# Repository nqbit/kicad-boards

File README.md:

# kicad-boards

### BeMicro Max 10 Development Board Template

Created a little board template for http://www.alterawiki.com/wiki/BeMicro_Max_10.

### SWD Shifter

The ST-Link/V2 debugger does not perform level shifting properly, the SWD Shifter translates the levels appropriately from the the ST-Link debugger.

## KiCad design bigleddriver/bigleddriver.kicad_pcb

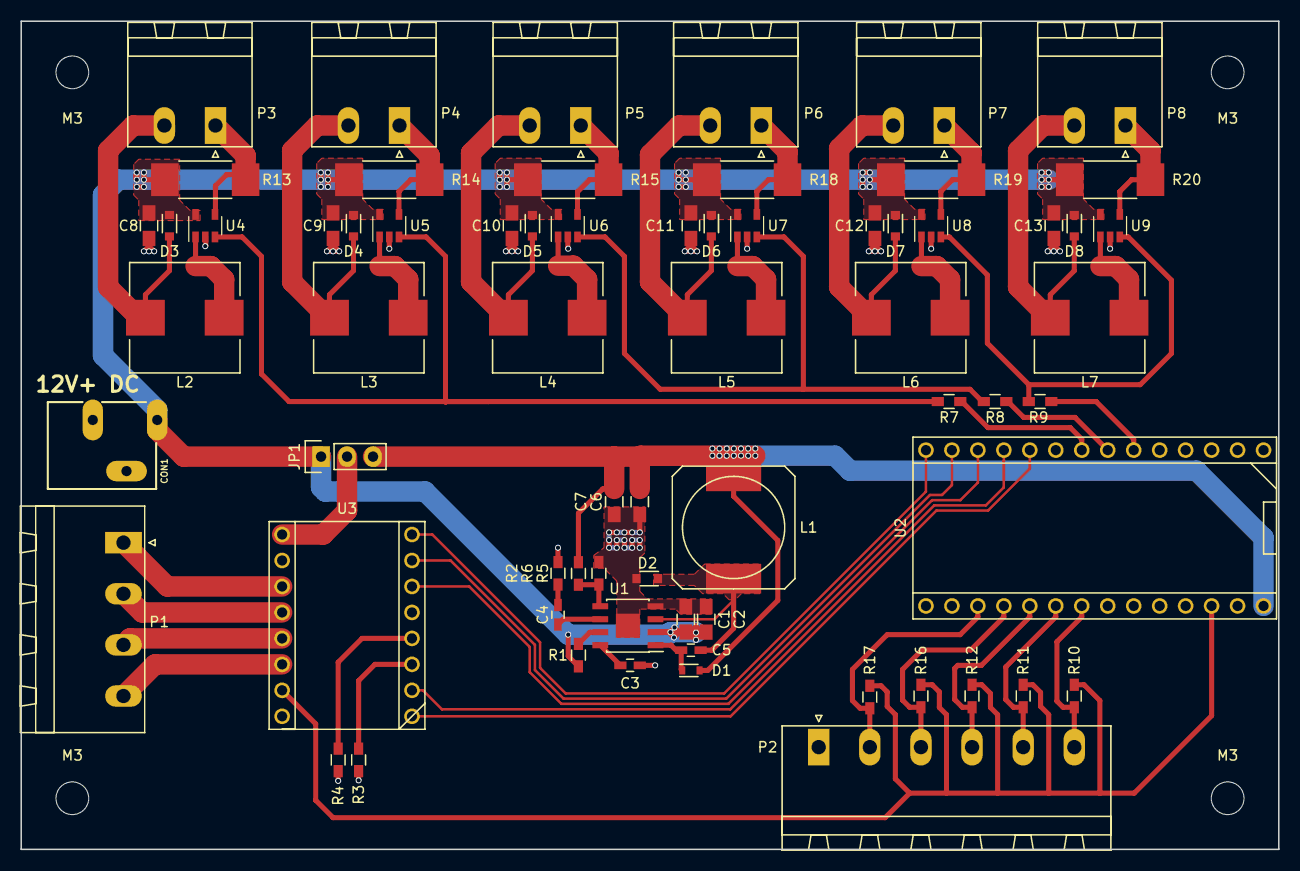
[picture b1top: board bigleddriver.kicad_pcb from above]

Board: 2 copper layers, 123.0 x 81.0 mm, 71 parts (0 on the bottom side), 52 nets.

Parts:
C1, C2, C8, C9, C10, C11, C12, C13: 10uF; C_0805_HandSoldering
C3: 0.1uF; C_0603_HandSoldering
C4: 3.9nF; C_0603_HandSoldering
C5: 10nF; C_0603_HandSoldering
C6, C7: 22uF; C_0805_HandSoldering
CON1: DC_BARREL_JACK; POWER_JACK_SLOT
D1: IN4148; D_0603
D2: MBRS130; D_0805
D3, D4, D5, D6, D7, D8: 1N5819; D_0805
JP1: Jumper_NC_Dual; Pin_Header_Straight_1x03
L1: 10uH; SELF-WE-PD-XXL
L2, L3, L4, L5, L6, L7: 100uH; Inductor_Wurth_HCI-1030
M3, M3#2, M3#3, M3#4: MountingHole_3.2mm_M3
P1: CONN_01X04; PhoenixContact_MSTBA-G_04x5.00mm_Angled
P2: CONN_01X06; PhoenixContact_MSTBA-G_06x5.00mm_Angled
P3, P4, P5, P6, P7, P8: CONN_01X02; PhoenixContact_MSTBA-G_02x5.00mm_Angled
R1: 100k; R_0603_HandSoldering
R2: 6.8k; R_0603_HandSoldering
R3, R4: 0; R_0603_HandSoldering
R5, R10, R11, R12, R16, R17: 10k; R_0603_HandSoldering
R6: 44.2k; R_0603_HandSoldering
R7, R8, R9: 22; R_0603_HandSoldering
R13, R14, R15, R18, R19, R20: 0.3; R_2512_HandSoldering
U1: MP2307; SOIC-8-1EP_3.9x4.9mm_Pitch1.27mm
U2: TEENSY_3.2
U3: STEP_STICK_TMC2208; TMC2208_SILENTSTEPSTICK
U4, U5, U6, U7, U8, U9: AL8861; SOT-23-5

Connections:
+5V: C6.1, C7.1, D1.2, JP1.3, L1.2, R6.2, U2.28
+12V: C1.1, C2.1, C8.1, C9.1, C10.1, C11.1, C12.1, C13.1, CON1.PWR, D3.1, D4.1, D5.1, D6.1, D7.1, D8.1, JP1.1, R1.2, R13.2, R14.2, R15.2, R18.2, R19.2, R20.2, U1.2, U4.5, U5.5, U6.5, U7.5, U8.5, U9.5
/BTN0: P2.6, R10.2, U2.21
/BTN1: P2.5, R11.2, U2.20
/BTN2: P2.4, R12.2, U2.19
/BTN3: P2.3, R16.2, U2.18
/BTN4: P2.2, R17.2, U2.17
/M1-A: P1.3, U3.13
/M1-B: P1.4, U3.14
/M2-A: P1.2, U3.12
/M2-B: P1.1, U3.11
/MOTOR_DIR: U2.10, U3.1
/MOTOR_EN: U2.14, U3.8
/MOTOR_MS1: U2.13, U3.7
/MOTOR_MS2: U2.12, U3.6
/MOTOR_STEP: U2.11, U3.2
/PWM_B: R9.1, U8.3, U9.3
/PWM_G: R8.1, U6.3, U7.3
/PWM_R: R7.1, U4.3, U5.3
/SW: C5.2, D2.1, L1.1, U1.3
/VIO: R10.1, R11.1, R12.1, R16.1, R17.1, U2.26, U3.15
GND: C1.2, C2.2, C3.2, C6.2, C7.2, C8.2, C9.2, C10.2, C11.2, C12.2, C13.2, CON1.GND@, D2.2, P2.1, R2.1, R3.2, R4.2, R5.2, U1.4, U1.9, U2.1, U2.27, U3.10, U3.16, U4.2, U5.2, U6.2, U7.2, U8.2, U9.2
unnamed: C3.1, U1.8
unnamed: C4.1, U1.6
unnamed: C4.2, R2.2
unnamed: C5.1, D1.1, U1.1
unnamed: D3.2, L2.2, P3.2
unnamed: D4.2, L3.2, P4.2
unnamed: D5.2, L4.2, P5.2
unnamed: D6.2, L5.2, P6.2
unnamed: D7.2, L6.2, P7.2
unnamed: D8.2, L7.2, P8.2
unnamed: L2.1, U4.1
unnamed: L3.1, U5.1
unnamed: L4.1, U6.1
unnamed: L5.1, U7.1
unnamed: L6.1, U8.1
unnamed: L7.1, U9.1
unnamed: P3.1, R13.1, U4.4
unnamed: P4.1, R14.1, U5.4
unnamed: P5.1, R15.1, U6.4
unnamed: P6.1, R18.1, U7.4
unnamed: P7.1, R19.1, U8.4
unnamed: P8.1, R20.1, U9.4
unnamed: R1.1, U1.7
unnamed: R3.1, U3.3
unnamed: R4.1, U3.4
unnamed: R5.1, R6.1, U1.5
unnamed: R7.2, U2.8
unnamed: R8.2, U2.7
unnamed: R9.2, U2.6
VMOTOR: JP1.2, U3.9

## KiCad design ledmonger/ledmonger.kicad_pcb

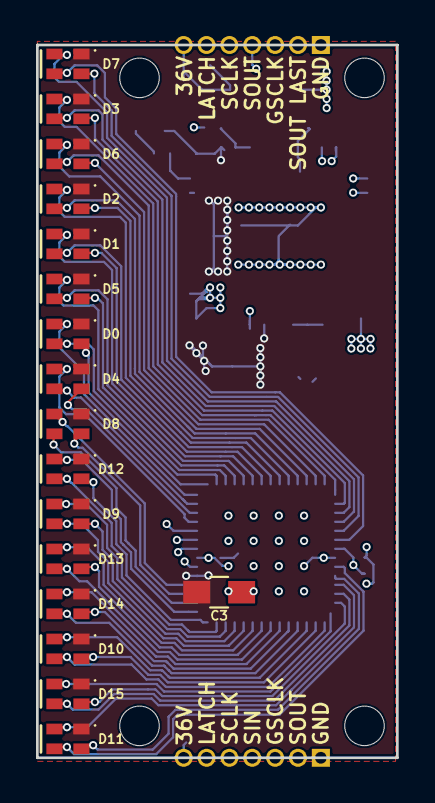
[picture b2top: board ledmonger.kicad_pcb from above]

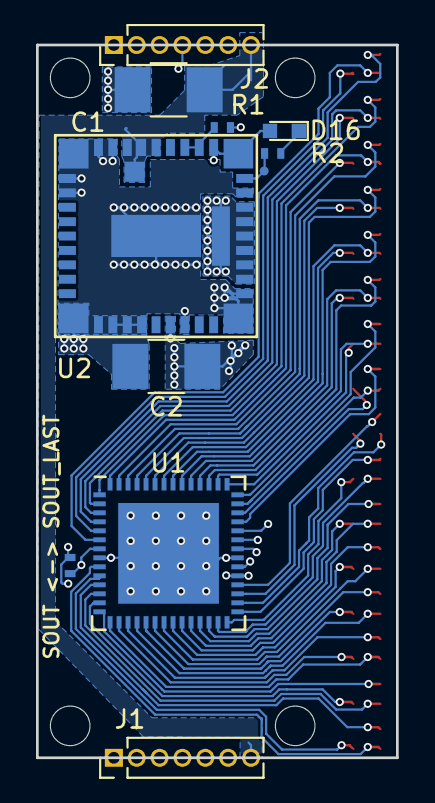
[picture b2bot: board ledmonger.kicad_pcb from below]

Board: 4 copper layers, 20.0 x 39.6 mm, 28 parts (11 on the bottom side), 60 nets.

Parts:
C1, C2: 100uF; C_1210_HandSoldering
C3: 100nF; C_0805_HandSoldering
D0, D1, D2, D3, D4, D5, D6, D7, D8, D9, D10, D11, D12, D13, D14, D15: LED_ARGB; LED_HSMF-C114
D16: LED_Small; LED_0603
J1, J2: Conn_01x07; Pin_Header_Straight_1x07_Pitch1.27mm
JP1: Jumper_NC_Small; R_0402_NoSilk
R1, R2: 8.06k; R_0402_NoSilk
TP0: PWRGD; TEST_POINT_0.5mm
U1: TLC5955; QFN-56-1EP_7x7mm_Pitch0.5mm
U2: LMZ34202; 43-BQFN-10mmx10mm

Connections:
+3V3: C2.1, C3.1, D0.1, D1.1, D2.1, D3.1, D4.1, D5.1, D6.1, D7.1, D8.1, D9.1, D10.1, D11.1, D12.1, D13.1, D14.1, D15.1, D16.2, U1.33, U2.7, U2.13, U2.14, U2.15, U2.16, U2.17, U2.18, U2.21, U2.22, U2.43
/GSCLK: J1.3, J2.3, U1.34
/LAT: J1.6, J2.6, U1.38
/LEDB0: D0.4, U1.42
/LEDB1: D1.4, U1.48
/LEDB2: D2.4, U1.51
/LEDB3: D3.4, U1.1
/LEDB4: D4.4, U1.39
/LEDB5: D5.4, U1.45
/LEDB6: D6.4, U1.54
/LEDB7: D7.4, U1.4
/LEDB8: D8.4, U1.32
/LEDB9: D9.4, U1.26
/LEDB10: D10.4, U1.17
/LEDB11: D11.4, U1.11
/LEDB12: D12.4, U1.29
/LEDB13: D13.4, U1.23
/LEDB14: D14.4, U1.20
/LEDB15: D15.4, U1.14
/LEDG0: D0.3, U1.44
/LEDG1: D1.3, U1.50
/LEDG2: D2.3, U1.53
/LEDG3: D3.3, U1.3
/LEDG4: D4.3, U1.41
/LEDG5: D5.3, U1.47
/LEDG6: D6.3, U1.56
/LEDG7: D7.3, U1.6
/LEDG8: D8.3, U1.30
/LEDG9: D9.3, U1.24
/LEDG10: D10.3, U1.15
/LEDG11: D11.3, U1.9
/LEDG12: D12.3, U1.27
/LEDG13: D13.3, U1.21
/LEDG14: D14.3, U1.18
/LEDG15: D15.3, U1.12
/LEDR0: D0.2, U1.43
/LEDR1: D1.2, U1.49
/LEDR2: D2.2, U1.52
/LEDR3: D3.2, U1.2
/LEDR4: D4.2, U1.40
/LEDR5: D5.2, U1.46
/LEDR6: D6.2, U1.55
/LEDR7: D7.2, U1.5
/LEDR8: D8.2, U1.31
/LEDR9: D9.2, U1.25
/LEDR10: D10.2, U1.16
/LEDR11: D11.2, U1.10
/LEDR12: D12.2, U1.28
/LEDR13: D13.2, U1.22
/LEDR14: D14.2, U1.19
/LEDR15: D15.2, U1.13
/PWRGD: R2.2, TP0.1, U2.20
/SCLK: J1.5, J2.5, U1.37
/SIN: J1.4, U1.36
/SOUT: J2.4, JP1.1, U1.7
/SOUT_LAST: J1.2, J2.2, JP1.2
/V36P0: C1.1, J1.7, J2.7, U2.26, U2.27, U2.28, U2.42
/VADJ: R1.2, U2.23, U2.24
GND: C1.2, C2.2, C3.2, J1.1, J2.1, R1.1, U1.8, U1.35, U1.57, U2.1, U2.2, U2.3, U2.4, U2.5, U2.8, U2.11, U2.12, U2.19, U2.29, U2.30, U2.31, U2.32, U2.33, U2.41
unnamed: D16.1, R2.1

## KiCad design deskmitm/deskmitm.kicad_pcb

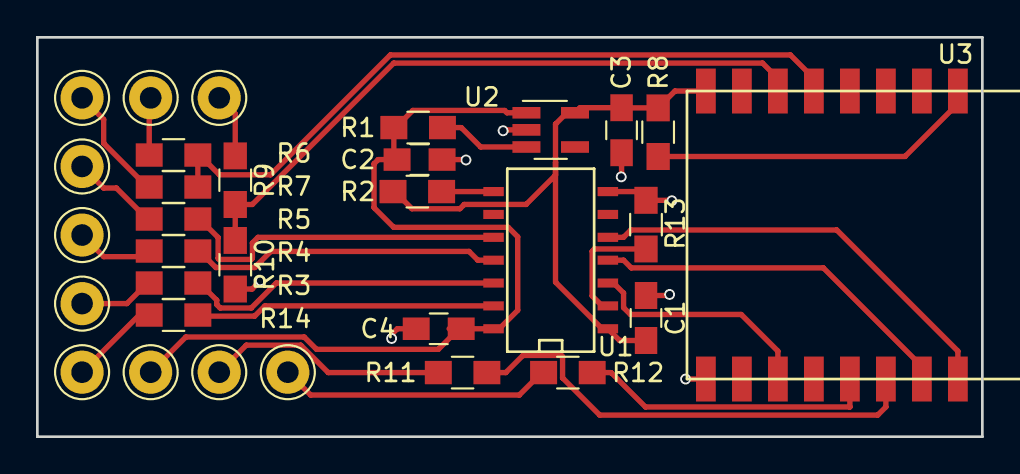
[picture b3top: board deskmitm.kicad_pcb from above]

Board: 2 copper layers, 52.5 x 22.2 mm, 31 parts (0 on the bottom side), 26 nets.

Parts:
C1, C4: 100nF; C_0805_HandSoldering
C2, C3: 10uF; C_0805_HandSoldering
J1, J2, J3, J4, J5, J6, J7, J8, J9, J10: Conn_01x01; Pin_d1.0mm_L10.0mm_LooseFit
R1, R2, R8, R11, R12, R13: 10k; R_0805_HandSoldering
R3, R4, R5, R6, R9, R14: 1k; R_0805_HandSoldering
R7, R10: 2k; R_0805_HandSoldering
U1: TXB0104; SOIC-14_N
U2: AP2112; SOT-23-5_HandSoldering
U3: ESP8266_12S; ESP8266_07

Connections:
+3V3: C1.1, C3.1, R2.2, R8.1, U1.1, U2.5, U3.8
+5V: C2.1, C4.1, J9.1, R1.2, U1.14, U2.1
/BTN_DOWN_IN: J1.1, R6.1
/BTN_DOWN_IN_LV: R6.2, R7.1, U3.5
/BTN_DOWN_OUT: J4.1, R12.1
/BTN_UP_IN: J2.1, R9.1
/BTN_UP_IN_LV: R9.2, R10.1, U3.6
/BTN_UP_OUT: J3.1, R11.1
/RX_FROM_POWER: J8.1, R5.1
/RX_FROM_POWER_LV: U1.5, U3.16
/RX_TO_DISPLAY: J5.1, R14.1
/RX_TO_DISPLAY_LV: R13.1, U1.2
/TX_FROM_POWER: J7.1, R4.1
/TX_FROM_POWER_LV: U1.4, U3.15
/TX_TO_DISPLAY: J6.1, R3.1
/TX_TO_DISPLAY_LV: U1.3, U3.11
GND: C1.2, C2.2, C3.2, C4.2, J10.1, R7.2, R10.2, R13.2, U1.7, U2.2, U3.9
unnamed: R1.1, U2.3
unnamed: R2.1, U1.8
unnamed: R3.2, U1.12
unnamed: R4.2, U1.11
unnamed: R5.2, U1.10
unnamed: R8.2, U3.1
unnamed: R11.2, U3.14
unnamed: R12.2, U3.13
unnamed: R14.2, U1.13

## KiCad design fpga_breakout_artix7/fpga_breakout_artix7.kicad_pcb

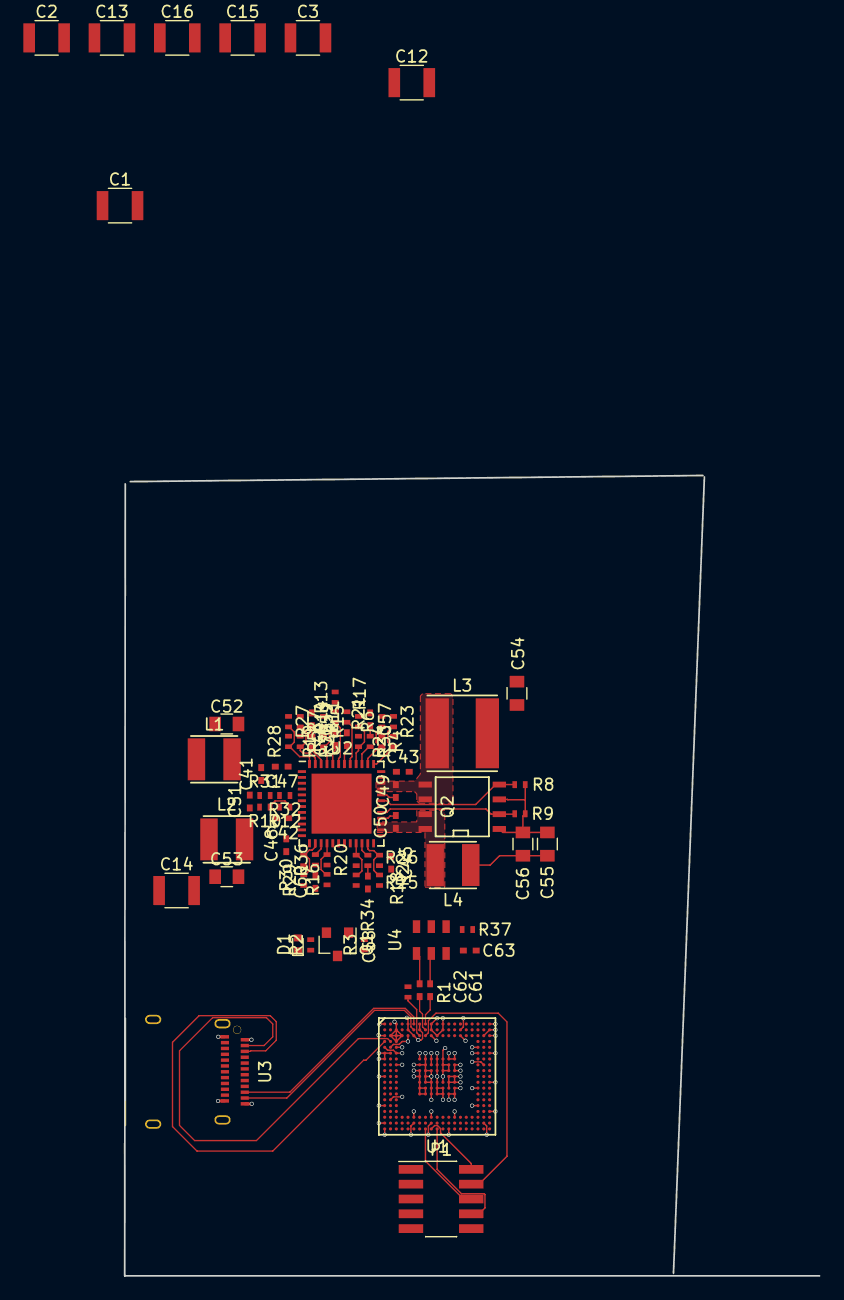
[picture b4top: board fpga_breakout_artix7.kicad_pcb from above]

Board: 4 copper layers, 59.6 x 68.6 mm, 112 parts (0 on the bottom side), 68 nets.

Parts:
C1, C13, C14, C15, C16: 100uF; C_1210
C2, C3, C12: 47uF; C_1210
C4, C6, C7, C8, C17, C18, C19, C20, C21, C22, C23, C24: 4.7uF; C_0805
C5, C9, C10, C11, C25, C26, C27, C28, C29, C30, C31, C32, C33, C34, C35, C36, C37, C38, C39, C40: 0.47uF; C_0603
C41, C42, C43, C44, C45, C46, C51: 1uF; C_0402_NoSilk
C47, C48, C49, C50, C61, C62, C63: 100nF; C_0402_NoSilk
C52, C53: 10uF; C_0805
C54: 100uF; C_0805
C55, C56: 22uF; C_0805
C57, C58, C59, C60: 2.7nF; C_0402_NoSilk
D1: LED; LED_0402
L1, L2: 4.7uH; SRN4018
L3: 2.2uH; SRN6045
L4: 3.3uH; SRN4018
P1: CONN_02X05; Pin_Header_Straight_2x05_Pitch1.27mm_SMD
Q1: MOSFET-N; SOT-23
Q2: FDS9926A; SOIC-8-N
R1: 100; R_0402_NoSilk
R2: 4.7k; R_0402_NoSilk
R3: 100k; R_0402_NoSilk
R4, R13: 0; R_0402_NoSilk
R5: 301k; R_0402_NoSilk
R6: 9.53k - DNP; R_0402_NoSilk
R7: 402k; R_0402_NoSilk
R8, R9: 47k; R_0402_NoSilk
R10: 1.91k; R_0402_NoSilk
R11, R17: 31.6k; R_0402_NoSilk
R12: 4.99k; R_0402_NoSilk
R14: 0 - DNP; R_0402_NoSilk
R15, R18: 10.5k; R_0402_NoSilk
R16, R21: 10.2k; R_0402_NoSilk
R19, R22: 41.2k; R_0402_NoSilk
R20: 20k; R_0402_NoSilk
R23, R24, R25, R26, R27, R28, R29, R30, R31, R32, R33, R34, R35, R36: 56.2k; R_0402_NoSilk
R37: 10k; R_0402_NoSilk
U1: XC7A15TCPG236; CPG236
U2: ADP5052; QFN-48-1EP_7x7mm_Pitch0.5mm
U3: USB-C; USB-C_SMT
U4: DSC1123

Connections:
/GTP0_RX_N: U1.A4, U3.B10
/GTP0_RX_P: U1.B4, U3.B11
/GTP0_TX_N: U1.D1, U3.A3
/GTP0_TX_P: U1.D2, U3.A2
/GTP1_RX_N: U1.A6, U3.A10
/GTP1_RX_P: U1.B6, U3.A11
/GTP1_TX_N: U1.A2, U3.B3
/GTP1_TX_P: U1.B2, U3.B2
/GTP_REF_CLK_N: C61.1, U1.A8
/GTP_REF_CLK_P: C62.1, U1.B8
/JTAG_TCK: P1.4, U1.C8
/JTAG_TDI: P1.8, U1.W10
/JTAG_TDO: P1.6, U1.W8
/JTAG_TMS: P1.2, U1.W9
/VCC3V3: C63.2, P1.1, R37.1, U4.6
/power/AVCC1V0: C52.1, L1.2, R15.1
/power/AVCC1V2: C53.1, L2.2, R16.1
/power/BST1: C49.1, U2.32
/power/BST2: C50.1, U2.28
/power/COMP1: R33.2, U2.39
/power/COMP2: R34.2, U2.22
/power/COMP3: R35.2, U2.46
/power/COMP4: R36.2, U2.15
/power/DL1: Q2.4, R8.2, U2.31
/power/DL2: Q2.2, R9.2, U2.29
/power/EN1: R23.2, R24.1, U2.37
/power/EN2: R25.2, R26.1, U2.23
/power/EN3: R27.2, R28.1, U2.48
/power/EN4: R29.2, R30.1, U2.14
/power/EN5: R31.2, R32.1, U2.5
/power/FB1: R17.2, R21.1, U2.40
/power/FB2: R18.2, R22.1, U2.21
/power/FB3: R15.2, R19.1, U2.45
/power/FB4: R16.2, R20.1, U2.16
/power/FB5: R10.1, R12.1, U2.6
/power/SS12: R4.2, R6.1, U2.38
/power/SS34: R5.2, R7.2, U2.47
/power/SW1: C49.2, L3.1, Q2.5, Q2.6, U2.33, U2.34
/power/SW2: C50.2, L4.1, Q2.7, Q2.8, U2.26, U2.27
/power/SW3: C47.2, L1.1, U2.3
/power/SW4: C48.2, L2.1, U2.10
/power/VCC1V0: C55.1, C56.1, L4.2, R18.1
/power/VCC1V8: C51.1, R12.2, U2.7
/power/VCC3V3: C54.1, D1.2, L3.2, R3.1, R17.1, R23.1, R25.1, R27.1, R29.1, R31.1, U2.8
/power/VCC5V0: C41.1, C42.1, C43.1, C45.1, U2.4, U2.9, U2.24, U2.25, U2.35, U2.36
/power/VREG: C44.1, R6.2, R7.1, R13.2, U2.44
AVCC1P0: U1.C1, U1.E1, U1.F3, U1.G9, U1.H9
AVCC1P2: R1.2, U1.B1, U1.C5, U1.E2, U1.G7
GND: C1.2, C2.2, C3.2, C4.2, C5.2, C6.2, C7.2, C8.2, C9.2, C10.2, C11.2, C12.2, C13.2, C14.2, C15.2, C16.2, C17.2, C18.2, C19.2, C20.2, C21.2, C22.2, C23.2, C24.2, C25.2, C26.2, C27.2, C28.2, C29.2, C30.2, C31.2, C32.2, C33.2, C34.2, C35.2, C36.2, C37.2, C38.2, C39.2, C40.2, C41.2, C42.2, C43.2, C44.2, C45.2, C46.2, C51.2, C52.2, C53.2, C54.2, C55.2, C56.2, C57.1, C58.1, C59.1, C60.1, C63.1, P1.3, P1.5, P1.9, Q1.3, Q2.1, Q2.3, R4.1, R5.1, R8.1, R9.1, R10.2, R11.2, R14.2, R19.2, R20.2, R21.2, R22.2, R24.2, R26.2, R28.2, R30.2, R32.2, U1.A1, U1.A3, U1.A5, U1.A7, U1.A9, U1.A11, U1.A19, U1.B3, U1.B5, U1.B7, U1.B9, U1.B11, U1.B14, U1.C2, U1.C3, U1.C4, U1.C6, U1.C10, U1.C19, U1.D3, U1.E3, U1.E17, U1.F1, U1.F2, U1.F19, U1.G1, U1.G8, U1.G11, U1.H7, U1.H8, U1.H11, U1.H12, U1.H18, U1.J8, U1.J9, U1.J11, U1.J12, U1.K8, U1.L8, U1.L9, U1.L11, U1.L19, U1.M9, U1.M13, U1.N9, U1.N12, U1.N13, U1.P2, U1.T19, U1.U6, U1.U9, U1.V18, U1.W1, U1.W12, U2.2, U2.11, U2.13, U2.17, U2.18, U2.19, U2.30, U2.49, U3.A1, U3.A12, U3.B1, U3.B12, U3.P, U4.3
unnamed: C46.1, U2.42
unnamed: C47.1, U2.1
unnamed: C48.1, U2.12
unnamed: C57.2, R33.1
unnamed: C58.2, R34.1
unnamed: C59.2, R35.1
unnamed: C60.2, R36.1
unnamed: C61.2, U4.5
unnamed: C62.2, U4.4
unnamed: D1.1, R2.1
unnamed: Q1.1, R3.2, U2.20
unnamed: Q1.2, R2.2
unnamed: R1.1, U1.C7
unnamed: R11.1, U2.41
unnamed: R13.1, R14.1, U2.43
unnamed: R37.2, U4.1
V1P0: C1.1, C2.1, C4.1, C5.1, C7.1, C9.1, C11.1, U1.G10, U1.H10, U1.J10, U1.L10, U1.M10, U1.M11, U1.N10, U1.N11
V1P8: C3.1, C6.1, C8.1, C10.1, U1.C9, U1.H13, U1.J13
V3P3: C12.1, C13.1, C14.1, C15.1, C16.1, C17.1, C18.1, C19.1, C20.1, C21.1, C22.1, C23.1, C24.1, C25.1, C26.1, C27.1, C28.1, C29.1, C30.1, C31.1, C32.1, C33.1, C34.1, C35.1, C36.1, C37.1, C38.1, C39.1, C40.1, U1.B19, U1.C14, U1.C18, U1.F17, U1.G12, U1.G13, U1.H3, U1.J7, U1.K1, U1.K7, U1.K12, U1.K13, U1.L7, U1.L12, U1.L13, U1.M7, U1.M8, U1.M12, U1.M17, U1.N7, U1.N8, U1.R1, U1.R17, U1.U13, U1.V1, U1.V6, U1.V9

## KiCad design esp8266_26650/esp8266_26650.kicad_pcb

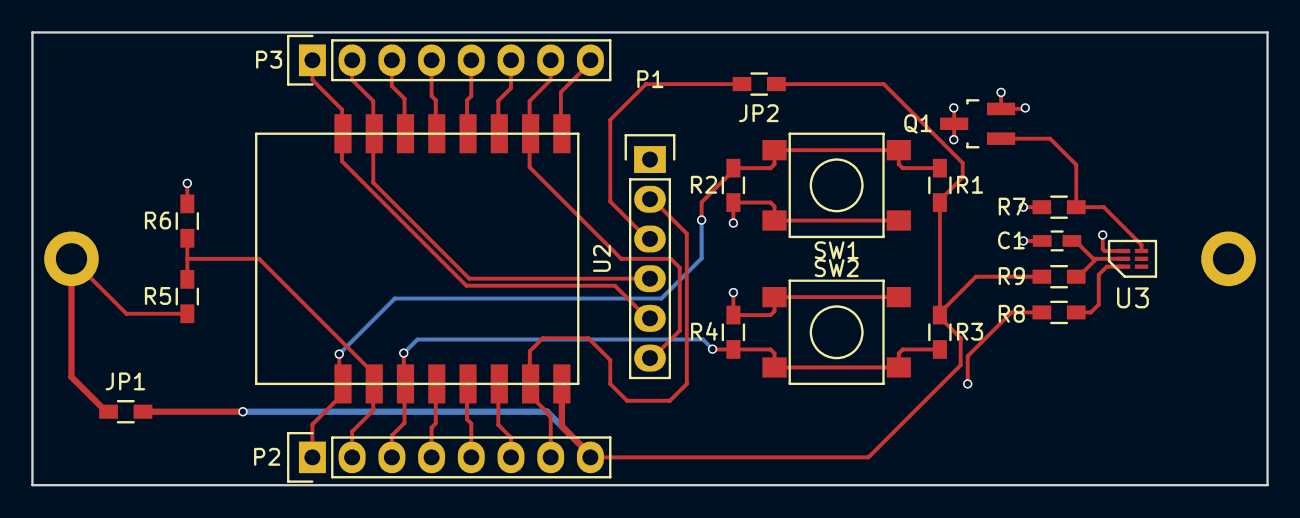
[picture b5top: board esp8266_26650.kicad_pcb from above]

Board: 2 copper layers, 79.0 x 29.0 mm, 21 parts (1 on the bottom side), 22 nets.

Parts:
C1: 0.1uF; C_0603_HandSoldering
JP1, JP2: JUMPER; R_0603_HandSoldering
P1: CONN_01X06; Pin_Header_Straight_1x06
P2, P3: CONN_01X08; Pin_Header_Straight_1x08
Q1: MMBF170; SOT-23_Handsoldering
R1, R2, R3, R4: 10k; R_0603_HandSoldering
R5: 260k; R_0603_HandSoldering
R6: 100k; R_0603_HandSoldering
R7: 5.1M; R_0603_HandSoldering
R8: 2.2k; R_0603_HandSoldering
R9: 330; R_0603_HandSoldering
SW1, SW2: SW_PUSH; B3S-1000P
U1: BATT_26650x1
U2: ESP8266_07
U3: BQ29705; WFDFN-6

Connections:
+BATT: JP1.1, R5.1, U1.1
/CH_PD: P2.3, R3.2, R4.1, SW2.2, U2.3
/DOUT: Q1.1, R7.1, U3.3
/FTDI_CTS: P1.2, P2.7, U2.7
/FTDI_RTS: P1.6, P3.7, U2.10
/FTDI_RX: P1.5, P3.1, U2.16
/FTDI_TX: P1.4, P3.2, U2.15
/FTDI_VCC: JP2.2, P1.3
/GPIO0: P3.5, U2.12
/GPIO1: P3.6, U2.11
/GPIO4: P3.4, U2.13
/GPIO5: P3.3, U2.14
/GPIO12: P2.6, U2.6
/GPIO14: P2.5, U2.5
/RESET: P2.1, R1.2, R2.1, SW1.2, U2.1
/VBAT_MON: P2.2, R5.2, R6.1, U2.2
/WAKE: P2.4, U2.4
GND: P1.1, P3.8, Q1.3, R2.2, R4.2, R6.2, R8.1, SW1.1, SW2.1, U2.9
unnamed: C1.1, R9.2, U3.5
unnamed: R8.2, U3.6
VCC: JP1.2, JP2.1, P2.8, R1.1, R3.1, R9.1, U2.8
VSS: C1.2, Q1.2, R7.2, U1.2, U3.4

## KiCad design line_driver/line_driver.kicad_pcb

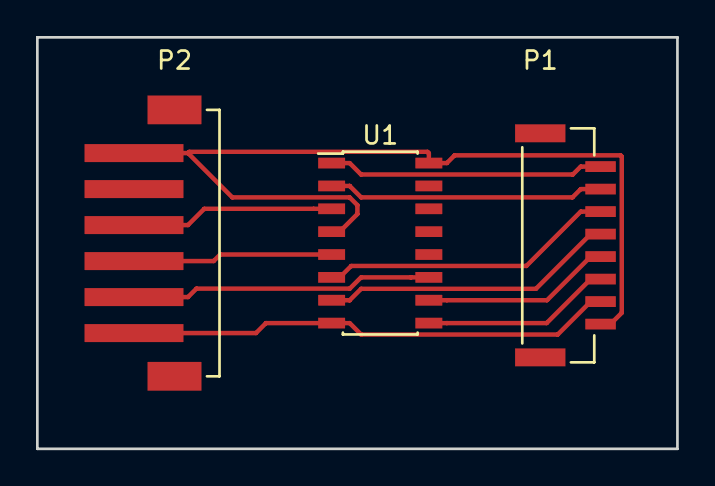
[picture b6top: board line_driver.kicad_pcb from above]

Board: 2 copper layers, 35.6 x 22.9 mm, 3 parts (0 on the bottom side), 11 nets.

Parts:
P1: CONN_01X08; GH_1x8_TOP
P2: CONN_01X06; CONN_PH_1x6_TOP_SMT
U1: AM26LS32ACDR; SOIC-16_3.9x9.9mm_Pitch1.27mm

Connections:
GND: P1.2, P2.6, U1.8
unnamed: P1.3, U1.9
unnamed: P1.4, U1.10
unnamed: P1.5, U1.7
unnamed: P1.6, U1.6
unnamed: P1.7, U1.2
unnamed: P1.8, U1.1
unnamed: P2.3, U1.3
unnamed: P2.4, U1.5
unnamed: P2.5, U1.11
VCC: P1.1, P2.1, U1.4, U1.16

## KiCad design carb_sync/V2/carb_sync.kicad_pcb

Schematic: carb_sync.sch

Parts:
12V1: 12V; Measurement_Point_Round-TH_Big
C1, C2, C3, C4, C5, C6: 100nF; C_0603_HandSoldering
C7, C8: C; c_elec_5x5.7
GND1: GND; Measurement_Point_Round-TH_Big
LCD1: ILI9341_Adafruit; ADAFRUIT_LCD
U1, U2, U3, U4, U5, U6: MPXV6115V
U7: TEENSY_3.2
U8: AP1117; TO-92_Horizontal1_Inline_Narrow_Oval

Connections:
+3V3: LCD1.3, U7.26
+5V: C8.1, LCD1.2, LCD1.39, U1.2 (VCC), U2.2 (VCC), U3.2 (VCC), U4.2 (VCC), U5.2 (VCC), U6.2 (VCC), U7.28, U8.2
+12V: 12V1.1, C7.1, U8.3
GND: C1.2, C2.2, C3.2, C4.2, C5.2, C6.2, C7.2, C8.2, GND1.1, LCD1.1, LCD1.40, U1.3 (GND), U2.3 (GND), U3.3 (GND), U4.3 (GND), U5.3 (GND), U6.3 (GND), U7.1, U7.27, U8.1
LCD_CLK: LCD1.4, U7.15
LCD_CS: LCD1.7, U7.12
LCD_D/C: LCD1.8, U7.11
LCD_MISO: LCD1.5, U7.14
LCD_MOSI: LCD1.6, U7.13
LCD_RST: LCD1.9, U7.10
TOUCH_X+: LCD1.12, U7.17
TOUCH_X-: LCD1.14, U7.19
TOUCH_Y+: LCD1.11, U7.16
TOUCH_Y-: LCD1.13, U7.18
VAC1: C1.1, U1.4 (VOUT), U7.21
VAC2: C2.1, U2.4 (VOUT), U7.23
VAC3: C3.1, U3.4 (VOUT), U7.25
VAC4: C4.1, U4.4 (VOUT), U7.20
VAC5: C5.1, U5.4 (VOUT), U7.22
VAC6: C6.1, U6.4 (VOUT), U7.24

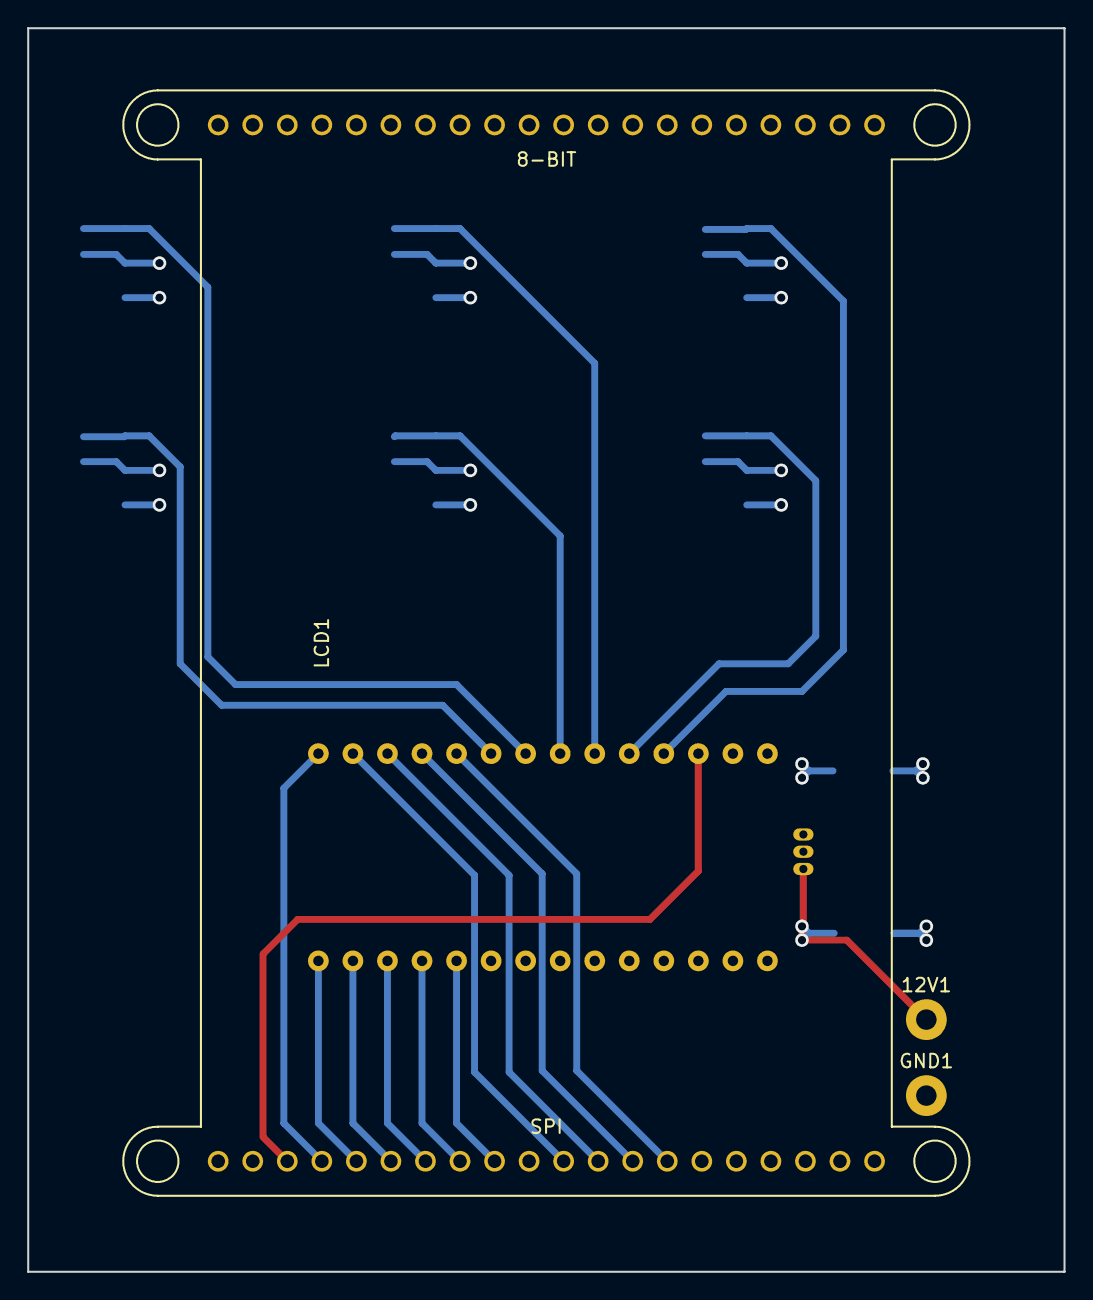
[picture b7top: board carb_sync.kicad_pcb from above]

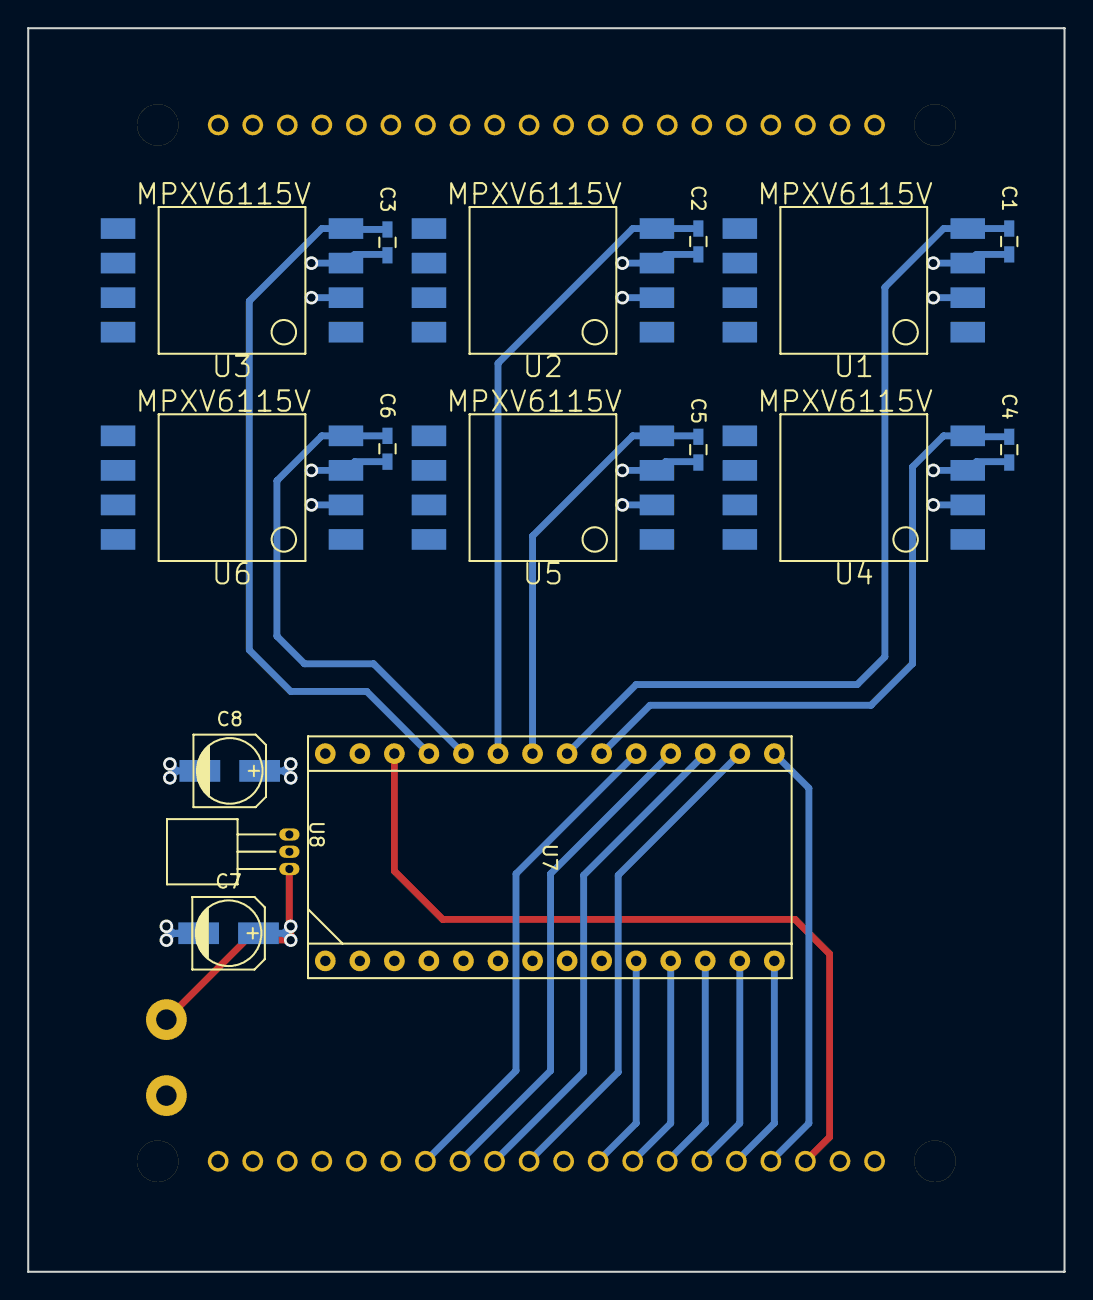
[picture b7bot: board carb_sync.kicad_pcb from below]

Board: 4 copper layers, 76.2 x 91.4 mm, 19 parts (16 on the bottom side), 20 nets.

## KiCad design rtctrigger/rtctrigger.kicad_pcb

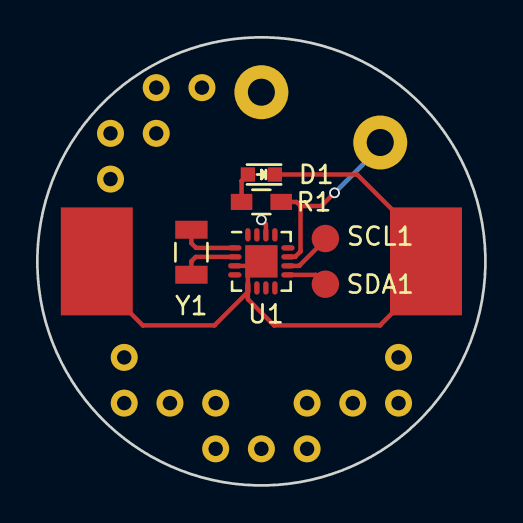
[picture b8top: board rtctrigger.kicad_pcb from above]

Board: 2 copper layers, 24.9 x 24.9 mm, 11 parts (1 on the bottom side), 8 nets.

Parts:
BATT1: BATT; PAD_7MM
BATT2: BATT; Measurement_Point_Round-TH_Big
D1: LED; LED_0603
GND1, GND2: GND; RECT_6X4MM
OUT1: OUT; Measurement_Point_Round-TH_Big
R1: 300; R_0603_HandSoldering
SCL1: SCL; Measurement_Point_Round-SMD-Pad_Small
SDA1: SDA; Measurement_Point_Round-SMD-Pad_Small
U1: M41T62; QFN-16-1EP_3x3mm_Pitch0.5mm
Y1: Crystal_Small; FC-135

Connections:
+BATT: BATT1.1, BATT2.1, U1.14
GND: D1.1, GND1.1, GND2.1, U1.3, U1.5, U1.17
unnamed: D1.2, R1.2
unnamed: OUT1.1, R1.1, U1.11
unnamed: SCL1.1, U1.10
unnamed: SDA1.1, U1.9
unnamed: U1.1, Y1.2
unnamed: U1.2, Y1.1

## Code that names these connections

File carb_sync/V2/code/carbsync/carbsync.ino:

#include <EEPROM.h>
#include <ILI9341_t3.h>
#include <SPI.h>
#include <TouchScreen.h>

#define MEM_MAGIC_ADDRESS 0
#define MEM_MAGIC_VALUE 0xDEADBEEF
#define SMOOTH_FACTOR_DEFAULT 0.99
#define SMOOTH_FACTOR_ADDRESS 4
#define SCALE_FACTOR_DEFAULT 0.3
#define SCALE_FACTOR_ADDRESS 8

#define DISP_X_OFFSET 0
#define DISP_Y_OFFSET 5
#define DISP_BAR_WIDTH 20
#define DISP_BAR_SPACING 20

#define FAST_DISP_X_OFFSET 20
#define FAST_DISP_Y_OFFSET 5
#define FAST_DISP_BAR_WIDTH 10
#define FAST_DISP_BAR_SPACING 30

#define VAC1 A5
#define VAC2 A7
#define VAC3 A9
#define VAC4 A4
#define VAC5 A6
#define VAC6 A8

// These are the four touchscreen analog pins
#define YP A0  // must be an analog pin, use "An" notation!
#define XM A3  // must be an analog pin, use "An" notation!
#define YM 16   // can be a digital pin
#define XP 15   // can be a digital pin

// This is calibration data for the raw touch data to the screen coordinates
#define TS_MINX 150
#define TS_MINY 120
#define TS_MAXX 920
#define TS_MAXY 940

#define MINPRESSURE 10
#define MAXPRESSURE 1000

#define TFT_DC  9
#define TFT_CS 10
#define TFT_SCLK 13
#define TFT_MOSI 11
#define TFT_MISO 12
#define TFT_RST 8

float SMOOTH_FACTOR = 0.99;
float LAST_SMOOTH_FACTOR = 0.99;
float SCALE_FACTOR = 0.3;
float LAST_SCALE_FACTOR = 0.3;

ILI9341_t3 tft = ILI9341_t3(TFT_CS, TFT_DC, TFT_RST, TFT_MOSI, TFT_SCLK, TFT_MISO);
TouchScreen ts = TouchScreen(XP, YP, XM, YM, 300);

float vac[6];
float vac_smooth[6] = {1023, 1023, 1023, 1023, 1023, 1023};
float vac_last[6];
float vac_smooth_last[6];
int vac_lu[] = {VAC1, VAC2, VAC3, VAC4, VAC5, VAC6};

enum Mode { Entry, Display, Config };

Mode mode = Display;
Mode last_mode = Entry;

class Button {
  public:
    Button(int x, int y, int w, int h) {
      _x = x;
      _y = y;
      _w = w;
      _h = h;
    }

    void draw() {
      uint16_t color = touched ? ILI9341_GREEN : ILI9341_YELLOW;
      tft.fillRoundRect(_x, _y, _w, _h, 10, color);
    }

    bool registerTouch(TSPoint p) {
      if (p.x < _x + _w && p.x > _x &&
          p.y < _y + _h && p.y > _y) {
        touched = true;
      } else {
        touched = false;
      }
      return touched;
    }

    bool isTouched() {
      return touched;
    }

  private:
    int _x;
    int _y;
    int _w;
    int _h;
    bool touched;
};

Button* buttons[4];

uint32_t getuint32(uint16_t addr)
{
  uint32_t val = 0;
  uint8_t val1 =  EEPROM.read(addr + 0) & 0xFF;
  uint8_t val2 =  EEPROM.read(addr + 1) & 0xFF;
  uint8_t val3 =  EEPROM.read(addr + 2) & 0xFF;
  uint8_t val4 =  EEPROM.read(addr + 3) & 0xFF;

  val = val1 | (val2 << 8) | (val3 << 16) | (val4 << 24);
  Serial.printf("getuint32: 0x%02x 0x%x 0x%x 0x%x 0x%02x\r\n", val1, val2, val3, val4, val);
  return val;
}

void setuint32(uint16_t addr, uint32_t val)
{
  uint8_t val1 = (val >> 0) & 0xFF;
  uint8_t val2 = (val >> 8) & 0xFF;
  uint8_t val3 = (val >> 16) & 0xFF;
  uint8_t val4 = (val >> 24) & 0xFF;

  EEPROM.write(addr + 0, val1);
  EEPROM.write(addr + 1, val2);
  EEPROM.write(addr + 2, val3);
  EEPROM.write(addr + 3, val4);

  Serial.printf("setuint32: 0x%02x 0x%02x 0x%02x 0x%02x 0x%02x\r\n", val1, val2, val3, val4, val);
}

void writeValues()
{
  setuint32(SMOOTH_FACTOR_ADDRESS, *((uint32_t*) &SMOOTH_FACTOR));
  setuint32(SCALE_FACTOR_ADDRESS, *((uint32_t*) &SCALE_FACTOR));
}

void writeMagic()
{
  setuint32(MEM_MAGIC_ADDRESS, (uint32_t) MEM_MAGIC_VALUE);
}


void readValues()
{
  uint32_t val1 = getuint32(SMOOTH_FACTOR_ADDRESS);
  uint32_t val2 = getuint32(SCALE_FACTOR_ADDRESS);
  SMOOTH_FACTOR = max(0.0, min(1.0, (float) * ((float*) &val1)));
  SCALE_FACTOR = max(0.0, min(1.0, (float) * ((float*) &val2)));
  LAST_SMOOTH_FACTOR = SMOOTH_FACTOR;
  LAST_SCALE_FACTOR = SCALE_FACTOR;
}

void restoreValues()
{
  uint32_t magic = getuint32(MEM_MAGIC_ADDRESS);

  if (magic != MEM_MAGIC_VALUE) {
    SMOOTH_FACTOR = SMOOTH_FACTOR_DEFAULT;
    SCALE_FACTOR = SCALE_FACTOR_DEFAULT;
    writeValues();
    writeMagic();
    Serial.println("Found NO magic");
  } else {
    readValues();
    Serial.println("Found magic");
  }
}
void setup(void) {


  tft.begin();
  tft.fillScreen(ILI9341_BLACK);

  tft.setTextColor(ILI9341_YELLOW);
  tft.setTextSize(2);
  tft.println("CarbSync");
  delay(200);
  tft.setRotation(2);
  tft.fillScreen(ILI9341_BLACK);

  Serial.begin(9600);
  Serial.println(tft.height());
  Serial.println(tft.width());

  buttons[0] = new Button(10, 50, 90, 70);
  buttons[1] = new Button(110, 50, 90, 70);
  buttons[2] = new Button(10, 150, 90, 70);
  buttons[3] = new Button(110, 150, 90, 70);

  restoreValues();
}


void loop()
{
  bool handled = false;

  // Retrieve a point
  TSPoint p = ts.getPoint();
  p.x = map(p.x, TS_MINX, TS_MAXX, 0, tft.width());
  p.y = map(p.y, TS_MINY, TS_MAXY, 0, tft.height());

  if (mode == Display) {
    for (int i = 0; i < 6; i++) {
      vac_last[i] = vac[i];
      vac[i] = 1023 - analogRead(vac_lu[i]) + 1;
      vac_smooth_last[i] = vac_smooth[i];
      vac_smooth[i] = vac[i] * (1 - SMOOTH_FACTOR) + vac_smooth[i] * SMOOTH_FACTOR;
    }

    for (int i = 0; i < 6; i++) {
      tft.fillRect(DISP_X_OFFSET + i * (DISP_BAR_WIDTH + DISP_BAR_SPACING), DISP_Y_OFFSET, DISP_BAR_WIDTH, vac_smooth[i]*SCALE_FACTOR, ILI9341_WHITE);
      tft.fillRect(DISP_X_OFFSET + i * (DISP_BAR_WIDTH + DISP_BAR_SPACING), vac_smooth[i]*SCALE_FACTOR + DISP_Y_OFFSET, DISP_BAR_WIDTH, 100, ILI9341_BLACK);

      tft.fillRect(FAST_DISP_X_OFFSET + i * (FAST_DISP_BAR_WIDTH + FAST_DISP_BAR_SPACING), FAST_DISP_Y_OFFSET, FAST_DISP_BAR_WIDTH, vac[i]*SCALE_FACTOR, ILI9341_RED);
      tft.fillRect(FAST_DISP_X_OFFSET + i * (FAST_DISP_BAR_WIDTH + FAST_DISP_BAR_SPACING), vac[i]*SCALE_FACTOR + FAST_DISP_Y_OFFSET, FAST_DISP_BAR_WIDTH, 500, ILI9341_BLACK);
    }
  } else {
    if (mode != last_mode) {
      tft.fillScreen(ILI9341_BLACK);
      tft.println("  CarbSync Config");
      tft.setCursor(10, 30);
      tft.setTextColor(ILI9341_WHITE);
      tft.print("Smooth + : -");
      tft.setCursor(10, 130);
      tft.print("Scale + : -");
      delay(100);
    } else {

      for (int i = 0; i < 4; i++) {
        handled = handled || buttons[i]->registerTouch(p);
        buttons[i]->draw();
      }

      if (buttons[0]->isTouched()) {
        SMOOTH_FACTOR = min(1.0, SMOOTH_FACTOR + 0.001);
        tft.fillRect(10, 250, tft.width(), 20, ILI9341_BLACK);
      }
      if (buttons[1]->isTouched()) {
        SMOOTH_FACTOR = max(0.0, SMOOTH_FACTOR - 0.001);
        tft.fillRect(10, 250, tft.width(), 20, ILI9341_BLACK);
      }
      tft.setCursor(10, 250);
      tft.print("Smooth: ");
      tft.print(SMOOTH_FACTOR);

      if (buttons[2]->isTouched()) {
        SCALE_FACTOR = min(1.0, SCALE_FACTOR + 0.001);
        tft.fillRect(10, 270, tft.width(), 20, ILI9341_BLACK);
      }
      if (buttons[3]->isTouched()) {
        SCALE_FACTOR = max(0.0, SCALE_FACTOR - 0.001);
        tft.fillRect(10, 270, tft.width(), 20, ILI9341_BLACK);
      }
      tft.setCursor(10, 270);
      tft.print("Scale: ");
      tft.print(SCALE_FACTOR);

    }
  }

  last_mode = mode;

  // we have some minimum pressure we consider 'valid'
  // pressure of 0 means no pressing!
  if (p.z < MINPRESSURE || p.z > MAXPRESSURE || handled) {
    return;
  }

  Serial.println(mode);

  // Handle Touch
  switch (mode) {
    case Display:
      mode = Config;
      tft.setRotation(0);
      tft.fillScreen(ILI9341_BLACK);
      break;
    case Config:
      mode = Display;
      if (LAST_SMOOTH_FACTOR != SMOOTH_FACTOR ||
          LAST_SCALE_FACTOR != SCALE_FACTOR) {
        writeValues();
      }
      LAST_SCALE_FACTOR = SCALE_FACTOR;
      LAST_SMOOTH_FACTOR = SMOOTH_FACTOR;
      tft.setRotation(2);
      tft.fillScreen(ILI9341_BLACK);
      break;
  }

  delay(500);
}

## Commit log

2015-01-31 [max10_template] Initial commit of the Altera BeMicro Max 10 development board.
2015-01-31 [readme] Initial commit.
2015-02-08 [carb_sync] Initial commit... WIP
2015-02-09 [carb_sync] Initial complete layout. LCD connector to pads.
2015-02-10 [carb_sync] Changed crystal footprint for ATMEGA328P.
2015-05-02 [arduino_template] Initial commit of the arduino template.
2015-05-02 [carb_sync] Upload of the released board files sent to fab.
2015-05-02 [scripts] Added a little helper script that renames the kicad generated gerbers.
2015-05-02 [boost_regulator_simple] Initial commit of a simple boost regulator.
    Currently incomplete, calculations and README to come.
2015-05-02 [boost_regulator_simple] First pass layout complete.
2015-05-02 [tools] Added a .gitignore file.
2015-05-02 [boost_regulator_simple] Updated schematic descriptions.
2015-05-02 [boost_regulator_simple] Added schematic pdf.
2015-05-02 [boost_regulator_simple] Cleaned up backup files from project.
2015-05-02 [boost_regulator_simple] Made changes to reduce EMI and other cosmetics.
2015-05-02 [tools] Updated gitignore to ignore more.
2015-05-02 [boost_regulator_simple] Extended Q1 copper pour ground plane and fixed silkscreen.
2015-05-02 [boost_regulator_simple] Added more filter caps to U1 and the inductor.
2015-05-02 [boost_regulator_simple] Off to fab!
2015-05-02 [boost_regulator_simple] Added full part datasheets and regenerated gerbers and schematic.
2015-05-03 [goproduino] Initial commit of the gopro connector breakout.
2015-10-06 [swd_shifter] Initial commit of the SWD shifter.
2015-10-06 [rfid-reader] Initial commit of the FSK demodulator circuit
2015-12-27 [dash_connector] Initial commit of the Amazon Dash debug connector breakout board.
2016-01-25 [swd_shifter] Add SWO line conversion from target to host.
2016-01-25 [swd_shifter] Added PDF schematic.
2016-02-09 [dash_connector] Fabbed board with MacroFab.
2016-02-09 [electricman] Fabbed with oshpark.
2016-02-09 [carb_sync] Move carb_sync v1 into separate folder.
2016-02-09 [carb_sync] Initial commit of V2. Still a work in progress.
2016-03-02 [rtctrigger] Initial commit of the rtc trigger board.
2016-03-02 [carb_sync] Add power supply filter caps and external voltage.
2016-03-05 [dash_connector] Fix pinout and add silkscreen.
2016-03-06 [dash_connector] Add new gerbers to connector.
2016-03-09 [line_driver] Initial commit of the diff/single line driver.
2016-03-12 [mini3d] initial commit of mini3d
2016-03-23 [mini3d] added current sensing
2016-03-23 [carbsync] V2: added code
2016-03-30 [carbsync] There are too many hacks to count
2016-03-31 [carbsync] Add persistent storage to variables.
2016-11-13 [esp8266_26650] initial commit
2016-11-27 [esp8266_26650] double checked footprint for esp and placed order.
2018-01-12 [fpga_breakout_artix7] Initial commit of the artix7 fpga gtp breakout board.
2018-01-30 [fpga_breakout_artix7] Added power supply and ufl connectors to schematic.
2018-02-02 [fpga_breakout_artix7] Progress on power supply schematic and layout.
2018-02-20 [fpga_breakout_artix7] Added USB-C connector, oscillator, and cleaned up power routing.
2018-05-28 [deskmitm] Initial commit of the desk mitm project.
2018-06-20 [ledmonger] Initial commit of the ledmonger.
    A basic breakout board for the TLC5955 led driver.
2018-06-26 [ledmonger] Improved layout and added castellated connector.
2018-06-27 [ledmonger] V1 ledmonger boards ordered.
2018-07-20 [qfn56pitchadapter] initial commit of 0.4 mm pitch to 0.5 mm pitch 56 pin + pad qfn adapter.
2018-07-20 [ledmonger] Added silkscreen to connectors. [ledmonger] Added dimensions to fab drawing. [ledmonger] Fixed floating INH/UVLO, tied to PVIN. [ledmonger] Fixed default resistor value for VADJ to be 3.5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
2019-04-01 [bigleddriver] Initial commit.
2019-04-03 [bigleddriver] Added digi-key part numbers.
2019-04-16 [bigleddriver] Minor changes and v0.1 was fabbed.
